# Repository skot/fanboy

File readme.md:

## Fanboy
warning: currently untested design!

RP2040 and EMC2103 dual channel USB fan controller. XT30 12V power connector.

- RP2040 Firmware to be based on [emberOne firmware](https://github.com/The-256-Foundation/ember-one-firmware)

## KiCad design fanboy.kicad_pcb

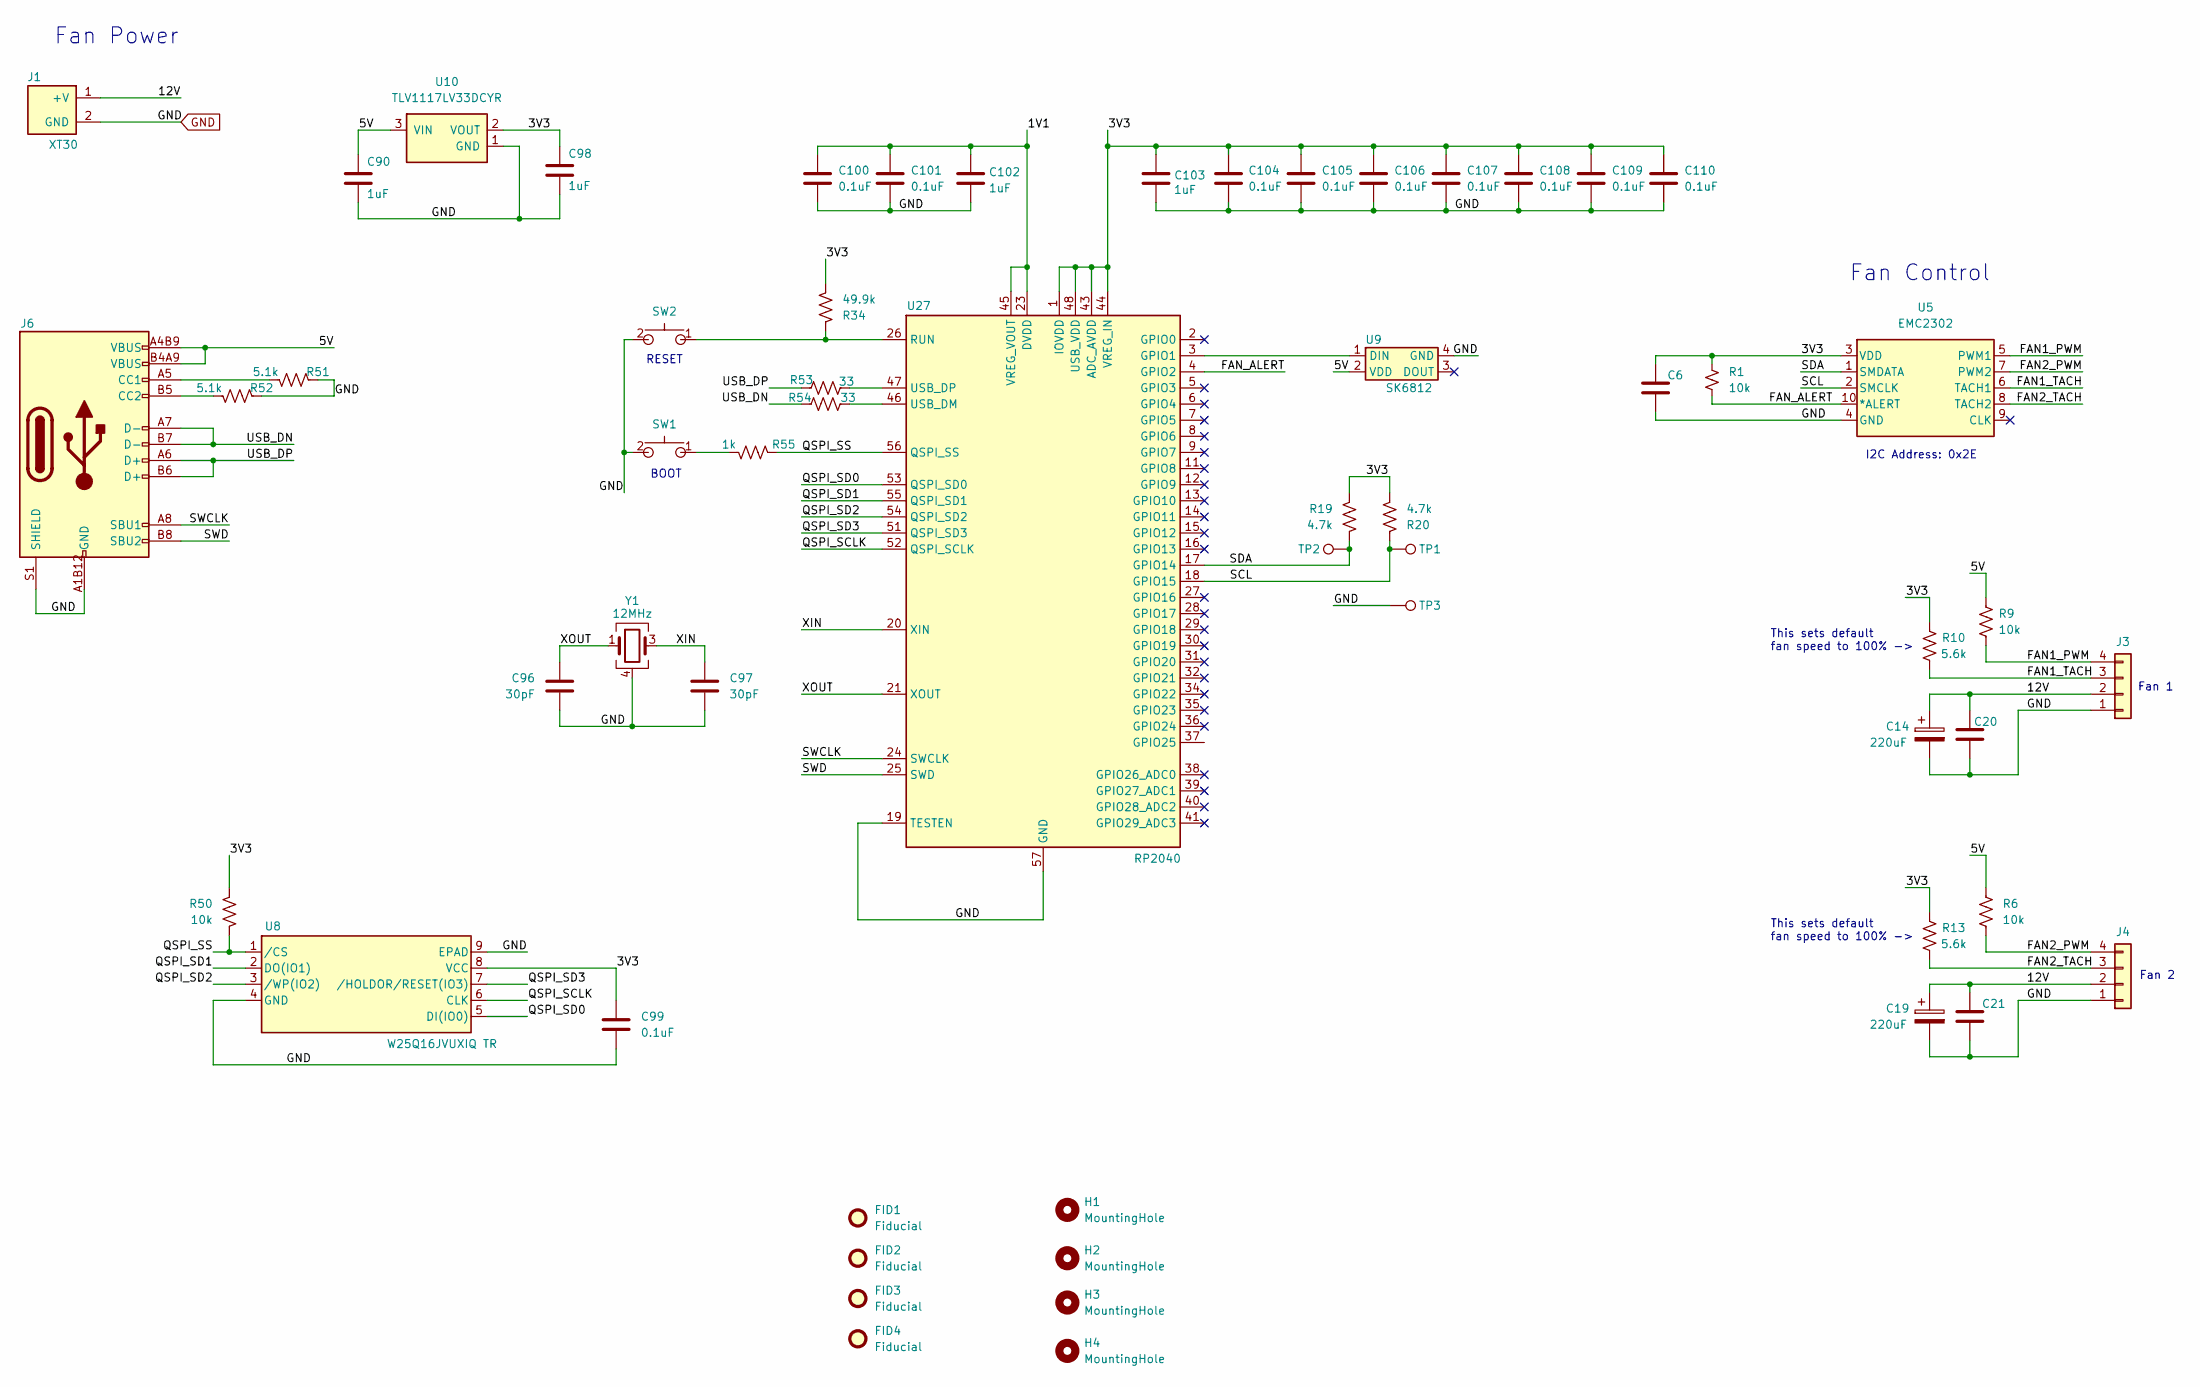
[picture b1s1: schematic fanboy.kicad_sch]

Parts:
C6, C20, C21: 311-3342-1-ND; C_0402_1005Metric; PARTNO KGM05AR71C104KH
C14, C19: 220uF; CP_Elec_6.3x7.7; PARTNO 865080345012
C90, C98, C102, C103: 1uF; C_0402_1005Metric; PARTNO EMK105BJ105MV-F; LCSC C52923
C96, C97: 30pF; C_0402_1005Metric; PARTNO GRM1555C1H300JA01D; LCSC C1570
C99, C100, C101, C104, C105, C106, C107, C108, C109, C110: 0.1uF; C_0402_1005Metric; PARTNO KGM05AR71C104KH; LCSC C307331
FID1, FID2, FID3, FID4: Fiducial; Fiducial_1mm_Mask2mm
H1, H2, H3, H4: MountingHole; MountingHole_3.5mm
J1: XT30; XT30PW-M; PARTNO XT30PW-M; LCSC C431092
J3, J4: Conn_01x04; 470531000; PARTNO 0470531000
J6: USB_C_Receptacle_USB2.0; USB_C_Receptacle_GCT_USB4105-xx-A_16P_TopMnt_Horizontal; PARTNO USB4105-GF-A; LCSC C2988369
R1, R6, R9: 10k; R_0402_1005Metric; PARTNO RC0402JR-0710KL
R10, R13: 5.6k; R_0402_1005Metric; PARTNO RC0402FR-135K6L
R19, R20: 4.7k; R_0402_1005Metric; PARTNO RC0402FR-074K7L
R34: 49.9k; R_0402_1005Metric; PARTNO RC0402FR-0749K9L
R50: 10k; R_0402_1005Metric; PARTNO RC0402JR-0710KL; LCSC C25744
R51, R52: 5.1k; R_0402_1005Metric; PARTNO RMCF0402JT5K10; LCSC C25905
R53, R54: 33; R_0402_1005Metric; PARTNO RC0402FR-0733RL; LCSC C25105
R55: 1k; R_0402_1005Metric; PARTNO RC0402FR-071KL; LCSC C106235
SW1, SW2: GT-TC029B-H025-L1N; SW_CS1213AGF260_CRS; PARTNO CS1213AGF260
TP1: SCL; TestPoint_Pad_D1.0mm
TP2: SDA; TestPoint_Pad_D1.0mm
TP3: GND; TestPoint_Pad_D1.0mm
U5: EMC2302; MSOP-10_3x3mm_P0.5mm; PARTNO EMC2302-2-AIZL-TR
U8: W25Q16JVUXIQ TR; USON-8_UX_2x3x0p6_WIN; PARTNO W25Q16JVUXIQ TR; LCSC C2843335
U9: SK6812; LED-SMD_4P-L4.0-W1.6-L; LCSC C2890037
U10: TLV1117LV33DCYR; VREG_TLV1117LV33DCYR; PARTNO TLV1117LV33DCYR
U27: RP2040; QFN-56-1EP_7x7mm_P0.4mm_EP3.2x3.2mm; PARTNO SC0914(13); LCSC C2040
Y1: 12MHz; XTAL_ECS-120-20-33-CKM-TR3; PARTNO ECS-120-20-33-CKM-TR3; LCSC C9002

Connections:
/1V1: C100.2, C101.2, C102.2, U27.23 (DVDD), U27.45 (VREG_VOUT), U27.50 (DVDD)
/3V3: C6.1, C98.1, C99.2, C103.2, C104.2, C105.2, C106.2, C107.2, C108.2, C109.2, C110.2, R1.2, R10.2, R13.2, R19.1, R20.2, R34.2, R50.1, U5.3 (VDD), U8.8 (VCC), U10.2 (VOUT), U10.4 (VOUT), U27.1 (IOVDD), U27.10 (IOVDD), U27.22 (IOVDD), U27.33 (IOVDD), U27.42 (IOVDD), U27.43 (ADC_AVDD), U27.44 (VREG_IN), U27.48 (USB_VDD), U27.49 (IOVDD)
/5V: C90.1, J6.A4B9 (VBUS), J6.B4A9 (VBUS), R6.2, R9.2, U9.2 (VDD), U10.3 (VIN)
/12V: C14.1, C19.1, C20.1, C21.1, J1.1 (+V), J3.2, J4.2
/FAN1_PWM: J3.4, R9.1, U5.5 (PWM1)
/FAN1_TACH: J3.3, R10.1, U5.6 (TACH1)
/FAN2_PWM: J4.4, R6.1, U5.7 (PWM2)
/FAN2_TACH: J4.3, R13.1, U5.8 (TACH2)
/FAN_ALERT: R1.1, U5.10 (*ALERT), U27.4 (GPIO2)
/QSPI_SCLK: U8.6 (CLK), U27.52 (QSPI_SCLK)
/QSPI_SD0: U8.5 (DI(IO0)), U27.53 (QSPI_SD0)
/QSPI_SD1: U8.2 (DO(IO1)), U27.55 (QSPI_SD1)
/QSPI_SD2: U8.3 (/WP(IO2)), U27.54 (QSPI_SD2)
/QSPI_SD3: U8.7 (/HOLDOR/RESET(IO3)), U27.51 (QSPI_SD3)
/QSPI_SS: R50.2, R55.1, U8.1 (/CS), U27.56 (QSPI_SS)
/SCL: R20.1, TP1.1, U5.2 (SMCLK), U27.18 (GPIO15)
/SDA: R19.2, TP2.1, U5.1 (SMDATA), U27.17 (GPIO14)
/SWCLK: J6.A8 (SBU1), U27.24 (SWCLK)
/SWD: J6.B8 (SBU2), U27.25 (SWD)
/USB_DN: J6.A7 (D-), J6.B7 (D-), R54.1
/USB_DP: J6.A6 (D+), J6.B6 (D+), R53.1
/XIN: C97.2, U27.20 (XIN), Y1.3
/XOUT: C96.2, U27.21 (XOUT), Y1.1
GND: C6.2, C14.2, C19.2, C20.2, C21.2, C90.2, C96.1, C97.1, C98.2, C99.1, C100.1, C101.1, C102.1, C103.1, C104.1, C105.1, C106.1, C107.1, C108.1, C109.1, C110.1, J1.2 (GND), J3.1, J4.1, J6.A1B12 (GND), J6.B1A12 (GND), J6.S1 (SHIELD), R51.1, R52.1, SW1.2, SW2.2, TP3.1, U5.4 (GND), U8.4 (GND), U8.9 (EPAD), U9.4 (GND), U10.1 (GND), U27.19 (TESTEN), U27.57 (GND), Y1.2, Y1.4
unnamed: J6.A5 (CC1), R51.2
unnamed: J6.B5 (CC2), R52.2
unnamed: R55.2, SW1.1
unnamed: U9.1 (DIN), U27.3 (GPIO1)
unnamed: R34.1, SW2.1, U27.26 (RUN)
unnamed: R54.2, U27.46 (USB_DM)
unnamed: R53.2, U27.47 (USB_DP)

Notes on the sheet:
Fan 2
BOOT
This sets default fan speed to 100% ->
Fan 1
RESET
Fan Control
Fan Power
This sets default fan speed to 100% ->
I2C Address: 0x2E

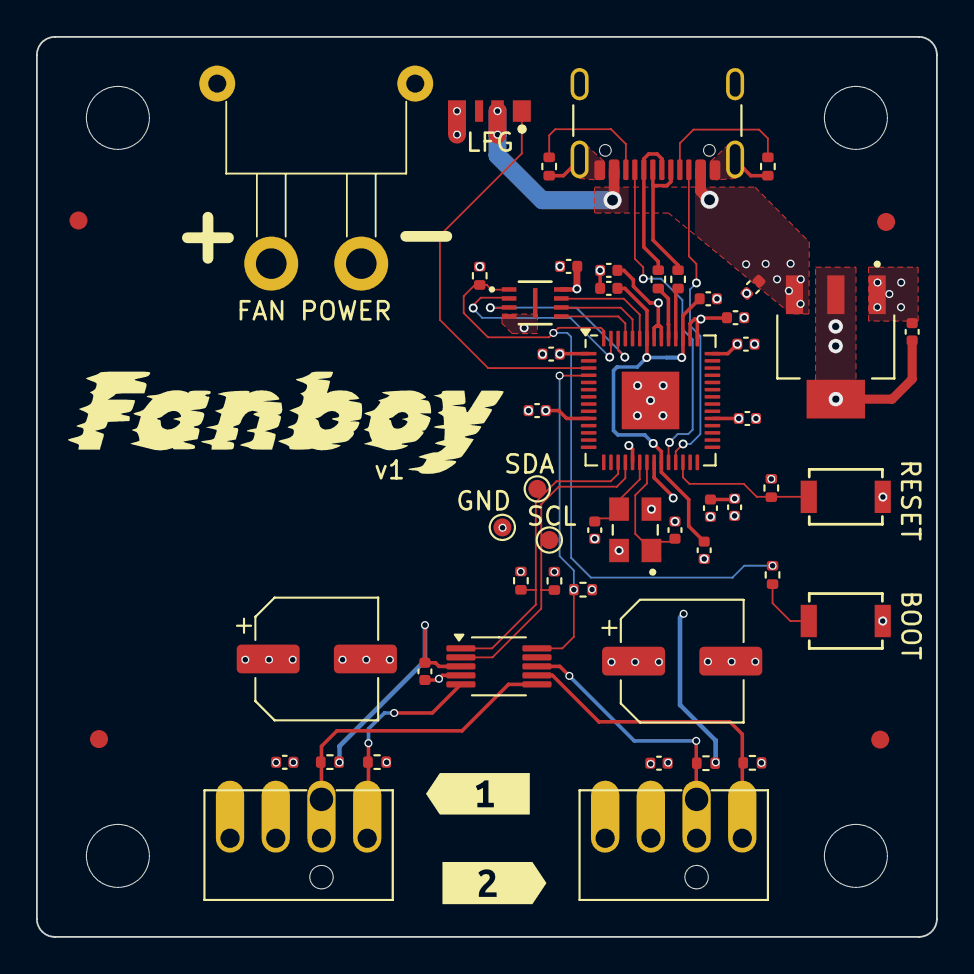
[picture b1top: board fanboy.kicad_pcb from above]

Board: 6 copper layers, 50.0 x 50.0 mm, 60 parts (0 on the bottom side), 31 nets.

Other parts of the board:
kibuzzard-68D5627E: G***; kibuzzard-68D5627E
kibuzzard-68D56264: G***; kibuzzard-68D56264

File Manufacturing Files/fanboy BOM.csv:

"Reference","Qty","Value","PARTNO","DK"
"C6,C20,C21","3","311-3342-1-ND","KGM05AR71C104KH","478-KGM05AR71C104KHCT-ND"
"C14,C19","2","220uF","865080345012","732-8422-1-ND"
"C90,C98,C102,C103","4","1uF","EMK105BJ105MV-F","587-5514-1-ND"
"C96,C97","2","30pF","GRM1555C1H300JA01D","490-5935-1-ND"
"C99,C100,C101,C104,C105,C106,C107,C108,C109,C110","10","0.1uF","KGM05AR71C104KH","478-KGM05AR71C104KHCT-ND"
"J1","1","XT30","XT30PW-M","~"
"J3,J4","2","Conn_01x04","0470531000","WM4330-ND"
"J6","1","USB_C_Receptacle_USB2.0","USB4105-GF-A","2073-USB4105-GF-ACT-ND"
"R1,R6,R9,R50","4","10k","RC0402JR-0710KL","311-10KJRCT-ND"
"R10,R13","2","5.6k","RC0402FR-135K6L","13-RC0402FR-135K6LCT-ND"
"R19,R20","2","4.7k","RC0402FR-074K7L","311-4.7KLRCT-ND"
"R34","1","49.9k","RC0402FR-0749K9L","311-49.9KLRCT-ND"
"R51,R52","2","5.1k","RMCF0402JT5K10","RMCF0402JT5K10CT-ND"
"R53,R54","2","33","RC0402FR-0733RL","311-33.0LRCT-ND"
"R55","1","1k","RC0402FR-071KL","311-1.00KLRCT-ND"
"SW1,SW2","2","GT-TC029B-H025-L1N","CS1213AGF260","2449-CS1213AGF260CT-ND"
"U5","1","EMC2302","EMC2302-2-AIZL-TR","EMC2302-2-AIZL-CT-ND"
"U8","1","W25Q16JVUXIQ TR","W25Q16JVUXIQ TR","256-W25Q16JVUXIQTRCT-ND"
"U9","1","SK6812","",""
"U10","1","TLV1117LV33DCYR","TLV1117LV33DCYR","296-28778-1-ND"
"U27","1","RP2040","SC0914(13)","2648-SC0914(13)CT-ND"
"Y1","1","12MHz","ECS-120-20-33-CKM-TR3","50-ECS-120-20-33-CKM-TR3CT-ND"

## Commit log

2025-09-24 initial import
2025-09-25 finished routing, added render and readme
2025-09-25 added BOM
2025-09-25 connect FAN_ALERT to EMC2103 and add pullup
2025-09-25 update BOM
2025-09-25 moved schematic symbols into separate library. added checked gerbers
2025-09-25 added mounting holes and fiducials. made board even 50x50mm. generated and checked gerbers
2025-09-25 updated render
2025-09-25 Add CERN Open Hardware Licence v2
    Added CERN Open Hardware Licence Version 2 - Strongly Reciprocal to the project.
